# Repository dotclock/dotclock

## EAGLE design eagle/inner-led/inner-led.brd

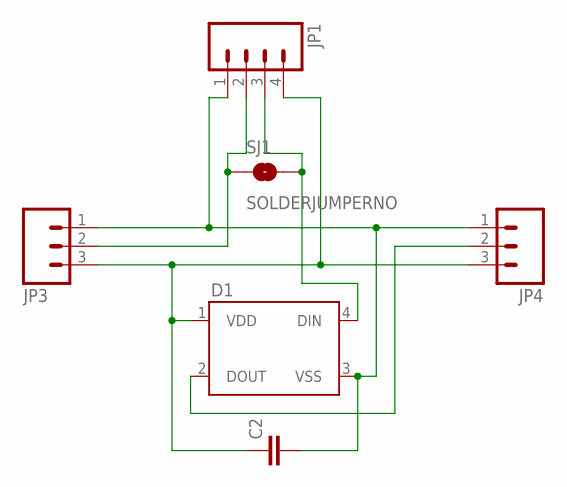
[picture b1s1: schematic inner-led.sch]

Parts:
C2: CAP0805; 0805
D1: WS2812B
JP1: M04NO_SILK_ALL_ROUND; 1X04_NO_SILK_ALL_ROUND
JP3, JP4: M031X03_NO_SILK; 1X03_NO_SILK
SJ1: SOLDERJUMPERNO; SJ_2S-NO

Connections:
unnamed: C2.1, D1.1 (VDD), JP1.4, JP3.3, JP4.3
unnamed: C2.2, D1.3 (VSS), JP1.1, JP3.1, JP4.1
unnamed: D1.2 (DOUT), JP4.2
unnamed: JP1.2, JP3.2, SJ1.1
unnamed: D1.4 (DIN), JP1.3, SJ1.2

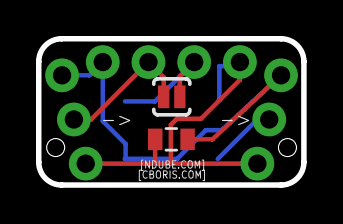
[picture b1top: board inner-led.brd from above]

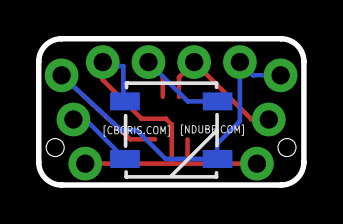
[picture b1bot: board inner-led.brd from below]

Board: 2 copper layers, 14.7 x 8.1 mm, 6 parts (2 on the bottom side), 5 nets.

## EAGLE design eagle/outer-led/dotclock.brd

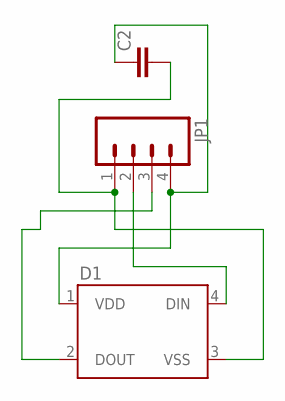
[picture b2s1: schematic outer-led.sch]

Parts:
C2: CAP0805; 0805
D1: WS2812B
JP1: M04NO_SILK_ALL_ROUND; 1X04_NO_SILK_ALL_ROUND

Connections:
unnamed: C2.2, D1.3 (VSS), JP1.1
unnamed: C2.1, D1.1 (VDD), JP1.4
unnamed: D1.4 (DIN), JP1.2
unnamed: D1.2 (DOUT), JP1.3

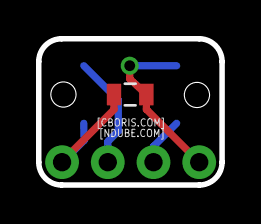
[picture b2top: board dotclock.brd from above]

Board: 2 copper layers, 10.2 x 8.1 mm, 3 parts (1 on the bottom side), 4 nets.

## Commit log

2016-11-03 Test commit
2016-11-03 Add gitignore
2016-11-03 Initial pcb checkin
2016-11-03 Rename board files

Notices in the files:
parts and their libraries:
SparkFun-LED: Licensing: Creative Commons ShareAlike 4.0 International - https://creativecommons.org/licenses/by-sa/4.0
